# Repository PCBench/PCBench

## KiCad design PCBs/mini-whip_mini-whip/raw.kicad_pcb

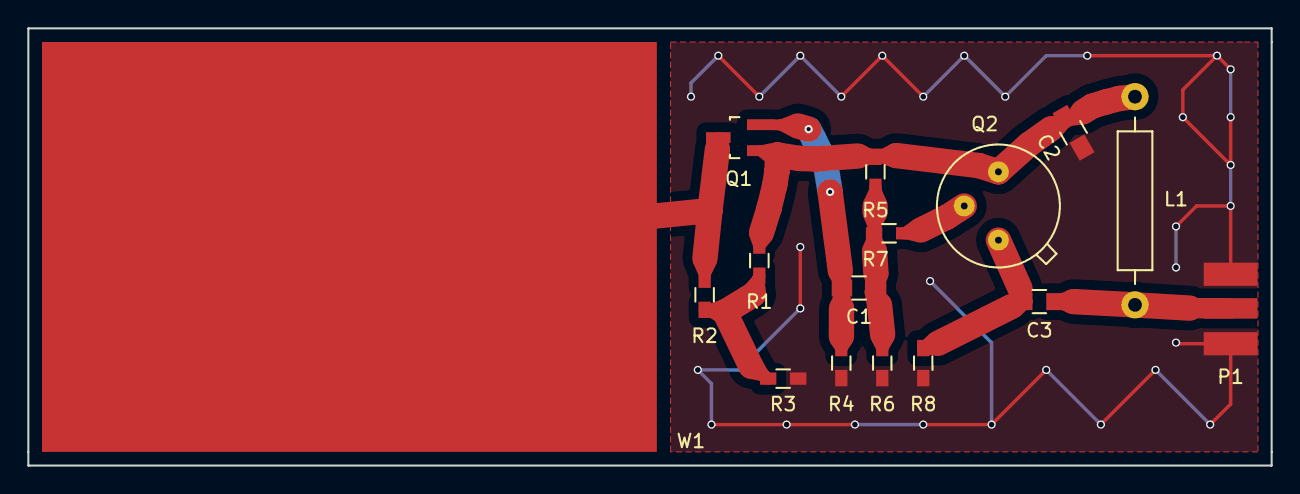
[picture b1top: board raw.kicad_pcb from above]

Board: 2 copper layers, 91.0 x 32.0 mm, 17 parts (1 on the bottom side), 9 nets.

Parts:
C1, C2, C3: 560n; C_0805_HandSoldering
L1: 470 uH; Choke_Horizontal_RM15mm
P1, P1#2: SMA-J
Q1: MMBFJ310; SOT-23_Handsoldering
Q2: 2N5109; M246
R1, R2, R3: 1M; R_0603_HandSoldering
R4: 680; R_0603_HandSoldering
R5: 2k2; R_0603_HandSoldering
R6: 10k; R_0603_HandSoldering
R7: 47; R_0603_HandSoldering
R8: 220; R_0603_HandSoldering
W1: MINIWHIP

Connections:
Earth: C2.1, P1.2, P1#2.2, R3.2, R4.2, R6.2, R8.2
unnamed: C1.1, R5.2, R6.1, R7.2
unnamed: C1.2, Q1.2, R4.1
unnamed: C2.2, L1.1, Q1.1, Q2.3, R1.1, R5.1
unnamed: C3.1, L1.2, P1.1, P1#2.1
unnamed: C3.2, Q2.1, R8.1
unnamed: Q1.3, R2.1, W1.1
unnamed: Q2.2, R7.1
unnamed: R1.2, R2.2, R3.1

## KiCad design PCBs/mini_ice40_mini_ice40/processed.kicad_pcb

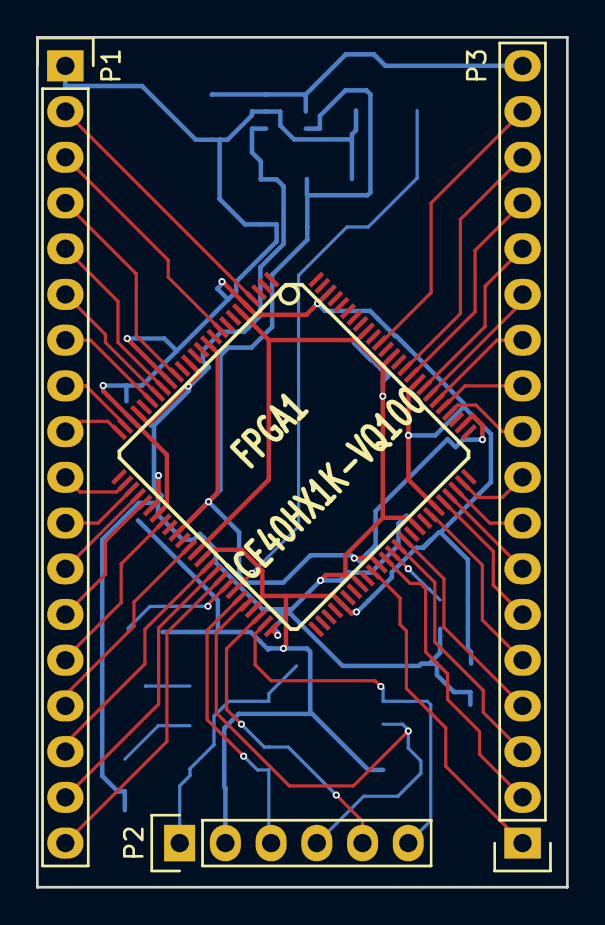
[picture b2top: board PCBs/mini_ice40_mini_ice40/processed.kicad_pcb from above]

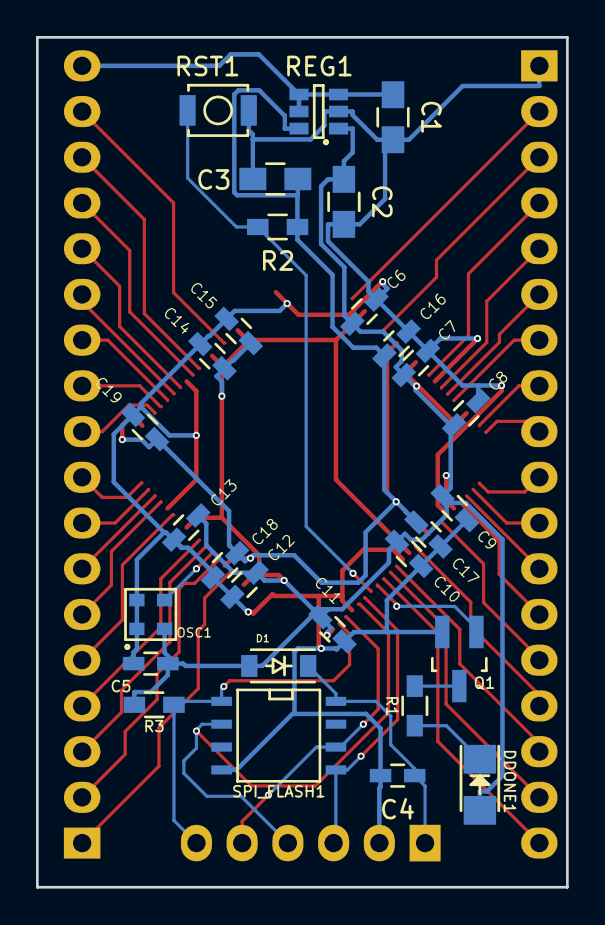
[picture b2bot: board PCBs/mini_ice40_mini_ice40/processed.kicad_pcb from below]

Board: 4 copper layers, 29.4 x 47.2 mm, 33 parts (29 on the bottom side), 48 nets.

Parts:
C1, C2, C3: 1u; C_0805_HandSoldering
C4, C5, C6, C7, C8, C9, C10, C11, C12, C13, C14, C15, C16, C17, C18, C19: 0u1; C_0603_HandSoldering
D1: 1N4448WQ-7-F; SOD-123
DDONE1: SML-LX1206GC-TR1; LED_1206
FPGA1: ICE40HX1K-VQ100; VQFP100
OSC1: ASDMB-26MHZ-LC; 2MMx2MM5
P1, P3: CONN_01X18; Pin_Header_Straight_1x18
P2: CONN_01X04; Pin_Header_Straight_1x06
Q1: 2N7002LT1G; SOT-23_Handsoldering
R1: 330; R_0603_HandSoldering
R2, R3: 10K; R_0603_HandSoldering
REG1: AP7312-1233W6-7; SOT-23-6
RST1: SW_PUSH; SW_SPST_B3U-1000P
SPI_FLASH1: AT25SF041-SSHD-B; SOIC-8-N

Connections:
+1V2: C3.1, C16.1, C17.1, C18.1, C19.1, FPGA1.11, FPGA1.35, FPGA1.61, FPGA1.77, R2.1, REG1.6
+3V3: C2.1, C5.1, C6.1, C7.1, C8.1, C9.1, C10.1, C11.1, C12.1, C13.1, C14.1, C15.1, D1.2, DDONE1.2, FPGA1.6, FPGA1.14, FPGA1.22, FPGA1.31, FPGA1.38, FPGA1.50, FPGA1.58, FPGA1.67, FPGA1.88, FPGA1.92, OSC1.4, R3.1, REG1.1
GND: C1.2, C2.2, C3.2, C4.2, C5.2, C6.2, C7.2, C8.2, C9.2, C10.2, C11.2, C12.2, C13.2, C14.2, C15.2, C16.2, C17.2, C18.2, C19.2, FPGA1.5, FPGA1.17, FPGA1.23, FPGA1.32, FPGA1.39, FPGA1.47, FPGA1.55, FPGA1.70, FPGA1.84, FPGA1.98, OSC1.1, OSC1.2, P1.1, P2.2, Q1.2, REG1.2, RST1.1, SPI_FLASH1.4
unnamed: C4.1, D1.1, P2.1, SPI_FLASH1.8
unnamed: DDONE1.1, R1.1
unnamed: FPGA1.4, P1.2
unnamed: FPGA1.9, P1.3
unnamed: FPGA1.16, P1.4
unnamed: FPGA1.18, P1.5
unnamed: FPGA1.19, P1.6
unnamed: FPGA1.20, P1.7
unnamed: FPGA1.24, P1.8
unnamed: FPGA1.25, P1.9
unnamed: FPGA1.27, P1.10
unnamed: FPGA1.28, P1.11
unnamed: FPGA1.29, P1.12
unnamed: FPGA1.30, P1.13
unnamed: FPGA1.33, P1.14
unnamed: FPGA1.37, P1.15
unnamed: FPGA1.40, P1.16
unnamed: FPGA1.41, P1.17
unnamed: FPGA1.42, P1.18
unnamed: FPGA1.43, Q1.1
unnamed: FPGA1.44, R2.2, RST1.2
unnamed: FPGA1.45, P2.3, SPI_FLASH1.5
unnamed: FPGA1.46, P2.4, SPI_FLASH1.2
unnamed: FPGA1.48, P2.5, SPI_FLASH1.6
unnamed: FPGA1.49, P2.6, R3.2, SPI_FLASH1.1
unnamed: FPGA1.60, P3.1
unnamed: FPGA1.62, P3.2
unnamed: FPGA1.63, OSC1.3
unnamed: FPGA1.64, P3.3
unnamed: FPGA1.65, P3.4
unnamed: FPGA1.69, P3.5
unnamed: FPGA1.71, P3.6
unnamed: FPGA1.72, P3.7
unnamed: FPGA1.73, P3.8
unnamed: FPGA1.74, P3.9
unnamed: FPGA1.79, P3.10
unnamed: FPGA1.80, P3.11
unnamed: FPGA1.81, P3.12
unnamed: FPGA1.82, P3.13
unnamed: FPGA1.83, P3.14
unnamed: FPGA1.85, P3.15
unnamed: FPGA1.86, P3.16
unnamed: FPGA1.90, P3.17
unnamed: Q1.3, R1.2
VCC: C1.1, P3.18, REG1.3, REG1.4, REG1.5

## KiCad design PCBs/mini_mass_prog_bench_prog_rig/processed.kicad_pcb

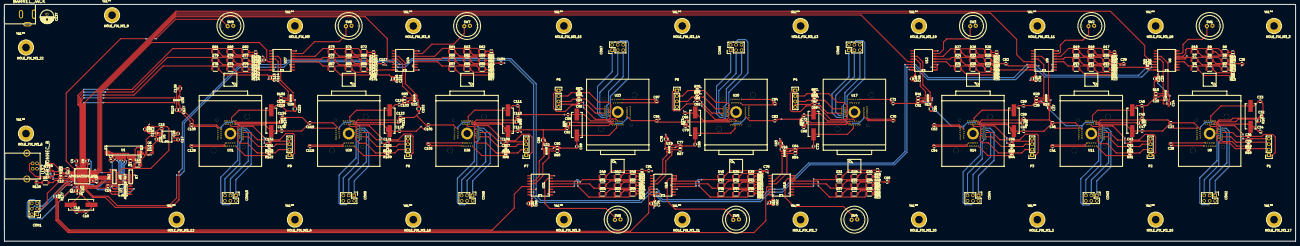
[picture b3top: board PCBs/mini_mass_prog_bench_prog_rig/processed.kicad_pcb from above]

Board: 4 copper layers, 600.0 x 110.0 mm, 441 parts (0 on the bottom side), 312 nets.

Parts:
C1, C2, C3, C4, C7, C8, C9, C10, C14, C15, C19, C22, C26, C27, C28, C29, C31, C32, C35, C39, C40, C41, C42, C44, C45, C48, C52, C53, C54, C55, C57, C58, C61, C65, C66, C67, C68, C70, C71, C74, C78, C79, C80, C81, C83, C84, C87, C91, C92, C93, C94, C96, C97, C100, C104, C105, C106, C107, C109, C110, C113, C117, C118, C119, C120, C122, C123, C128, C129, C130, C131, C133, C134, C135, C136: 100nF; C_0603
C5, C6: 22uF; C_1206
C11: 4.7uF; C_1206
C12, C25, C30, C38, C43, C51, C56, C64, C69, C77, C82, C90, C95, C103, C108, C116, C121, C127, C132: 1uF; C_0603
C13, C21: 4.7uF; C_0603
C16, C18, C33, C34, C46, C47, C59, C60, C72, C73, C85, C86, C98, C99, C111, C112, C124, C125: 18pF; C_0603
C17, C20: 220nF; C_0603
C23, C24, C36, C37, C49, C50, C62, C63, C75, C76, C88, C89, C101, C102, C114, C115, C126: 10uF; C_0805
C137: CP; C_Radial_D6.3_L11.2_P2.5
CON1, CON2, CON3, CON4, CON5, CON6, CON7, CON8, CON9, CON10: AVR-ISP-6; Pin_Header_Straight_2x03
CON11: BARREL_JACK; BARREL-PJ-002AH
D1, D2, D3, D4, D5, D6, D7, D8, D9, D10, D11, D12, D13, D14, D15, D16, D17, D18, D19, D20, D21, D22, D23, D24, D25, D26, D27, D28, D29, D30, D31, D32, D33, D34, D35, D36, D37, D38, D39, D40, D41, D42, D43, D44, D45, D46, D47, D48, D49, D50, D51, D52, D53, D54, D55, D56, D57, D58, D59, D60, D61, D62, D63, D64, D65, D66, D67, D68, D69, D70, D71, D72, D73, D74, D75, D76, D77, D78, D79, D80, D81, D82: LED; R_1206
HOLE_FIX_M3, HOLE_FIX_M3_2, HOLE_FIX_M3_3, HOLE_FIX_M3_4, HOLE_FIX_M3_5, HOLE_FIX_M3_6, HOLE_FIX_M3_7, HOLE_FIX_M3_8, HOLE_FIX_M3_9, HOLE_FIX_M3_10, HOLE_FIX_M3_11, HOLE_FIX_M3_12, HOLE_FIX_M3_13, HOLE_FIX_M3_14, HOLE_FIX_M3_15, HOLE_FIX_M3_16, HOLE_FIX_M3_17, HOLE_FIX_M3_18, HOLE_FIX_M3_19, HOLE_FIX_M3_20, HOLE_FIX_M3_21, HOLE_FIX_M3_22: VAL**; HOLE_FIX_M3
P1, P2, P3, P4, P5, P6, P7, P8, P9: CONN_01X04; Pin_Header_Straight_1x04
Q1: MOS_P; SOT23-3
R1: 910k; R_0603
R2, R3, R20, R33, R46, R59, R72, R85, R98, R111, R124, R127: 10k; R_0603
R4, R5, R18, R19, R31, R32, R44, R45, R57, R58, R70, R71, R83, R84, R96, R97, R109, R110, R122, R123: 22; R_0603
R6: 2k2; RNETWORK8_0603
R7: 4k7; RNETWORK8_0603
R8, R9, R10, R11, R12, R13, R14, R16, R17, R21, R22, R23, R24, R25, R26, R27, R29, R30, R34, R35, R36, R37, R38, R39, R40, R42, R43, R47, R48, R49, R50, R51, R52, R53, R55, R56, R60, R61, R62, R63, R64, R65, R66, R68, R69, R73, R74, R75, R76, R77, R78, R79, R81, R82, R86, R87, R88, R89, R90, R91, R92, R94, R95, R99, R100, R101, R102, R103, R104, R105, R107, R108, R112, R113, R114, R115, R116, R117, R118, R120, R121: R; R_0603
R15, R28, R41, R54, R67, R80, R93, R106, R119: 210k; R_0603
R125, R126: 2k2; R_0603
R128: 100; R_0603
SW1, SW2, SW3, SW4, SW5, SW6, SW7, SW8, SW9: SW_PUSH; SWITCH_K12P
U1: CON_UGM128032A6B01; CON_SFV24R-2STE1HLF
U2: ATMEGA32U4_QFN; QFN44
U3: AT45DB011D; SO8EN
U4: IP4234CZ6,125; TSOT-6-MK06A
U5: ST662ACD; SOIC-8-N
U6, U9, U12, U15, U18, U21, U24, U27: PCA9554; SO-16-L
U7, U10, U13, U16, U19, U22, U25, U28, U30: AP2552A; SOT-23-6
U8, U11, U14, U17, U20, U23, U26, U29, U31: ATMEGA32U4_QFN; QFN44_PROG_SOCKET
U32: USB_CONNEC_B; USB-AU-Y1007-R
Y1, Y2, Y3, Y4, Y5, Y6, Y7, Y8, Y9, Y10: 16MHz; Crystal_HC49-SD_SMD

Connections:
+3V3: C7.2, C12.1, C14.1, U1.5, U2.6, U3.3, U3.5, U3.6
+5V: C1.1, C2.1, C3.1, C4.1, C8.1, C13.1, C22.1, C23.1, C24.1, C26.1, C35.1, C36.1, C37.1, C39.1, C48.1, C49.1, C50.1, C52.1, C61.1, C62.1, C63.1, C65.1, C74.1, C75.1, C76.1, C78.1, C87.1, C88.1, C89.1, C91.1, C100.1, C101.1, C102.1, C104.1, C113.1, C114.1, C115.1, C117.1, C126.1, C128.1, C137.1, CON1.2, CON11.1, Q1.2, R2.1, R6.8, R8.1, R9.1, R10.1, R11.1, R12.1, R13.1, R14.1, R16.1, R17.1, R21.1, R22.1, R23.1, R24.1, R25.1, R26.1, R27.1, R29.1, R30.1, R34.1, R35.1, R36.1, R37.1, R38.1, R39.1, R40.1, R42.1, R43.1, R47.1, R48.1, R49.1, R50.1, R51.1, R52.1, R53.1, R55.1, R56.1, R60.1, R61.1, R62.1, R63.1, R64.1, R65.1, R66.1, R68.1, R69.1, R73.1, R74.1, R75.1, R76.1, R77.1, R78.1, R79.1, R81.1, R82.1, R86.1, R87.1, R88.1, R89.1, R90.1, R91.1, R92.1, R94.1, R95.1, R99.1, R100.1, R101.1, R102.1, R103.1, R104.1, R105.1, R107.1, R108.1, R112.1, R113.1, R114.1, R115.1, R116.1, R117.1, R118.1, R120.1, R121.1, R125.1, R126.1, U2.2, U2.14, U2.24, U2.34, U2.44, U6.16, U7.1, U9.1, U9.16, U10.1, U12.2, U12.16, U13.1, U15.1, U15.2, U15.16, U16.1, U18.3, U18.16, U19.1, U21.1, U21.3, U21.16, U22.1, U24.2, U24.3, U24.16, U25.1, U27.1, U27.2, U27.3, U27.16, U28.1, U30.1
+12V: C5.1, C6.1, C9.1, C19.1, C21.1, U1.23, U5.6
/BL_POWER: Q1.1, R6.7
/FLASH_HV_nS: R6.11, U2.28
/FLASH_nS: R6.6, R7.11, U3.4
/LCD_DnC: R6.3, R7.14, U1.10
/LCD_HV_DnC: R6.14, U2.25
/LCD_HV_SS: R6.12, U2.27
/LCD_HV_nRES: R6.13, U2.26
/LCD_SS: R6.5, R7.12, U1.8
/LCD_nRES: R6.4, R7.13, U1.9
/MISO: CON1.1, R127.1, U2.11
/MOSI: CON1.4, R3.1, U2.10
/Programming Socket #0/5V_SOCKET: C25.1, C27.1, C28.1, C29.1, C31.1, C32.1, CON2.2, R20.1, U7.6, U8.2, U8.14, U8.24, U8.34, U8.44
/Programming Socket #0/I2C_SCL: R125.2, U2.18, U6.14, U9.14, U12.14, U15.14, U18.14, U21.14, U24.14, U27.14
/Programming Socket #0/I2C_SDA: R126.2, U2.19, U6.15, U9.15, U12.15, U15.15, U18.15, U21.15, U24.15, U27.15
/Programming Socket #0/INT: U2.36, U6.13
/Programming Socket #0/LED1: D2.1, D3.1, D4.1, U6.4
/Programming Socket #0/LED2: D5.1, D6.1, D7.1, U6.5
/Programming Socket #0/LED3: D8.1, D9.1, D10.1, U6.6
/Programming Socket #0/PROG_MISO: CON2.1, U8.11
/Programming Socket #0/PROG_MOSI: CON2.4, U8.10
/Programming Socket #0/PROG_RESET: CON2.5, R20.2, U8.13
/Programming Socket #0/PROG_SCK: CON2.3, U8.9
/Programming Socket #0/PSU_EN: U6.11, U7.3
/Programming Socket #0/PSU_FAULT: U6.12, U7.4
/Programming Socket #0/SWITCH: SW1.1, U6.7
/Programming Socket #1/5V_SOCKET: C38.1, C40.1, C41.1, C42.1, C44.1, C45.1, CON3.2, R33.1, U10.6, U11.2, U11.14, U11.24, U11.34, U11.44
/Programming Socket #1/INT: U2.32, U9.13
/Programming Socket #1/LED1: D11.1, D12.1, D13.1, U9.4
/Programming Socket #1/LED2: D14.1, D15.1, D16.1, U9.5
/Programming Socket #1/LED3: D17.1, D18.1, D19.1, U9.6
/Programming Socket #1/PROG_MISO: CON3.1, U11.11
/Programming Socket #1/PROG_MOSI: CON3.4, U11.10
/Programming Socket #1/PROG_RESET: CON3.5, R33.2, U11.13
/Programming Socket #1/PROG_SCK: CON3.3, U11.9
/Programming Socket #1/PSU_EN: U9.11, U10.3
/Programming Socket #1/PSU_FAULT: U9.12, U10.4
/Programming Socket #1/SWITCH: SW2.1, U9.7
/Programming Socket #2/5V_SOCKET: C51.1, C53.1, C54.1, C55.1, C57.1, C58.1, CON4.2, R46.1, U13.6, U14.2, U14.14, U14.24, U14.34, U14.44
/Programming Socket #2/INT: U2.31, U12.13
/Programming Socket #2/LED1: D20.1, D21.1, D22.1, U12.4
/Programming Socket #2/LED2: D23.1, D24.1, D25.1, U12.5
/Programming Socket #2/LED3: D26.1, D27.1, D28.1, U12.6
/Programming Socket #2/PROG_MISO: CON4.1, U14.11
/Programming Socket #2/PROG_MOSI: CON4.4, U14.10
/Programming Socket #2/PROG_RESET: CON4.5, R46.2, U14.13
/Programming Socket #2/PROG_SCK: CON4.3, U14.9
/Programming Socket #2/PSU_EN: U12.11, U13.3
/Programming Socket #2/PSU_FAULT: U12.12, U13.4
/Programming Socket #2/SWITCH: SW3.1, U12.7
/Programming Socket #3/5V_SOCKET: C64.1, C66.1, C67.1, C68.1, C70.1, C71.1, CON5.2, R59.1, U16.6, U17.2, U17.14, U17.24, U17.34, U17.44
/Programming Socket #3/INT: R3.2, U15.13
/Programming Socket #3/LED1: D29.1, D30.1, D31.1, U15.4
/Programming Socket #3/LED2: D32.1, D33.1, D34.1, U15.5
/Programming Socket #3/LED3: D35.1, D36.1, D37.1, U15.6
/Programming Socket #3/PROG_MISO: CON5.1, U17.11
/Programming Socket #3/PROG_MOSI: CON5.4, U17.10
/Programming Socket #3/PROG_RESET: CON5.5, R59.2, U17.13
/Programming Socket #3/PROG_SCK: CON5.3, U17.9
/Programming Socket #3/PSU_EN: U15.11, U16.3
/Programming Socket #3/PSU_FAULT: U15.12, U16.4
/Programming Socket #3/SWITCH: SW4.1, U15.7
/Programming Socket #4/5V_SOCKET: C77.1, C79.1, C80.1, C81.1, C83.1, C84.1, CON6.2, R72.1, U19.6, U20.2, U20.14, U20.24, U20.34, U20.44
/Programming Socket #4/INT: R127.2, U18.13
/Programming Socket #4/LED1: D38.1, D39.1, D40.1, U18.4
/Programming Socket #4/LED2: D41.1, D42.1, D43.1, U18.5
/Programming Socket #4/LED3: D44.1, D45.1, D46.1, U18.6
/Programming Socket #4/PROG_MISO: CON6.1, U20.11
/Programming Socket #4/PROG_MOSI: CON6.4, U20.10
/Programming Socket #4/PROG_RESET: CON6.5, R72.2, U20.13
/Programming Socket #4/PROG_SCK: CON6.3, U20.9
/Programming Socket #4/PSU_EN: U18.11, U19.3
/Programming Socket #4/PSU_FAULT: U18.12, U19.4
/Programming Socket #4/SWITCH: SW5.1, U18.7
/Programming Socket #5/5V_SOCKET: C90.1, C92.1, C93.1, C94.1, C96.1, C97.1, CON7.2, R85.1, U22.6, U23.2, U23.14, U23.24, U23.34, U23.44
/Programming Socket #5/INT: U2.12, U21.13
/Programming Socket #5/LED1: D47.1, D48.1, D49.1, U21.4
/Programming Socket #5/LED2: D50.1, D51.1, D52.1, U21.5
/Programming Socket #5/LED3: D53.1, D54.1, D55.1, U21.6
/Programming Socket #5/PROG_MISO: CON7.1, U23.11
/Programming Socket #5/PROG_MOSI: CON7.4, U23.10
/Programming Socket #5/PROG_RESET: CON7.5, R85.2, U23.13
/Programming Socket #5/PROG_SCK: CON7.3, U23.9
/Programming Socket #5/PSU_EN: U21.11, U22.3
/Programming Socket #5/PSU_FAULT: U21.12, U22.4
/Programming Socket #5/SWITCH: SW6.1, U21.7
/Programming Socket #6/5V_SOCKET: C103.1, C105.1, C106.1, C107.1, C109.1, C110.1, CON8.2, R98.1, U25.6, U26.2, U26.14, U26.24, U26.34, U26.44
/Programming Socket #6/INT: U2.30, U24.13
/Programming Socket #6/LED1: D56.1, D57.1, D58.1, U24.4
/Programming Socket #6/LED2: D59.1, D60.1, D61.1, U24.5
/Programming Socket #6/LED3: D62.1, D63.1, D64.1, U24.6
/Programming Socket #6/PROG_MISO: CON8.1, U26.11
/Programming Socket #6/PROG_MOSI: CON8.4, U26.10
/Programming Socket #6/PROG_RESET: CON8.5, R98.2, U26.13
/Programming Socket #6/PROG_SCK: CON8.3, U26.9
/Programming Socket #6/PSU_EN: U24.11, U25.3
/Programming Socket #6/PSU_FAULT: U24.12, U25.4
/Programming Socket #6/SWITCH: SW7.1, U24.7
/Programming Socket #7/5V_SOCKET: C116.1, C118.1, C119.1, C120.1, C122.1, C123.1, CON9.2, R111.1, U28.6, U29.2, U29.14, U29.24, U29.34, U29.44
/Programming Socket #7/INT: U2.29, U27.13
/Programming Socket #7/LED1: D65.1, D66.1, D67.1, U27.4
/Programming Socket #7/LED2: D68.1, D69.1, D70.1, U27.5
/Programming Socket #7/LED3: D71.1, D72.1, D73.1, U27.6
/Programming Socket #7/PROG_MISO: CON9.1, U29.11
/Programming Socket #7/PROG_MOSI: CON9.4, U29.10
/Programming Socket #7/PROG_RESET: CON9.5, R111.2, U29.13
/Programming Socket #7/PROG_SCK: CON9.3, U29.9
/Programming Socket #7/PSU_EN: U27.11, U28.3
/Programming Socket #7/PSU_FAULT: U27.12, U28.4
/Programming Socket #7/SWITCH: SW8.1, U27.7
/Programming Socket #8/5V_SOCKET: C127.1, C129.1, C130.1, C131.1, C133.1, C134.1, CON10.2, R124.1, U30.6, U31.2, U31.14, U31.24, U31.34, U31.44
/Programming Socket #8/LED1: D74.1, D75.1, D76.1, U2.39
/Programming Socket #8/LED2: D77.1, D78.1, D79.1, U2.40
/Programming Socket #8/LED3: D80.1, D81.1, D82.1, U2.41
/Programming Socket #8/PROG_MISO: CON10.1, U31.11
/Programming Socket #8/PROG_MOSI: CON10.4, U31.10
/Programming Socket #8/PROG_RESET: CON10.5, R124.2, U31.13
/Programming Socket #8/PROG_SCK: CON10.3, U31.9
/Programming Socket #8/PSU_EN: U2.38, U30.3
/Programming Socket #8/PSU_FAULT: U2.37, U30.4
/Programming Socket #8/SWITCH: SW9.1, U2.1
/RESET: CON1.5, R2.2, U2.13
/SCK: CON1.3, U2.9
/SPI2_CLK: R6.2, R7.15, U1.13, U3.2
/SPI2_HV_MOSI: R6.16, U2.21
/SPI2_HV_SCK: R6.15, U2.22
/SPI2_MISO: U2.20, U3.8
/SPI2_MOSI: R6.1, R7.16, U1.14, U3.1
/USB_D+: R5.2, U2.4
/USB_D-: R4.2, U2.3
/USB_VBUS: C10.1, U2.7, U4.5, U32.1
GND: C1.2, C2.2, C3.2, C4.2, C5.2, C6.2, C7.1, C8.2, C9.2, C10.2, C11.2, C12.2, C13.2, C14.2, C15.2, C16.2, C18.2, C21.2, C22.2, C23.2, C24.2, C25.2, C26.2, C27.2, C28.2, C29.2, C30.2, C31.2, C32.2, C33.2, C34.2, C35.2, C36.2, C37.2, C38.2, C39.2, C40.2, C41.2, C42.2, C43.2, C44.2, C45.2, C46.2, C47.2, C48.2, C49.2, C50.2, C51.2, C52.2, C53.2, C54.2, C55.2, C56.2, C57.2, C58.2, C59.2, C60.2, C61.2, C62.2, C63.2, C64.2, C65.2, C66.2, C67.2, C68.2, C69.2, C70.2, C71.2, C72.2, C73.2, C74.2, C75.2, C76.2, C77.2, C78.2, C79.2, C80.2, C81.2, C82.2, C83.2, C84.2, C85.2, C86.2, C87.2, C88.2, C89.2, C90.2, C91.2, C92.2, C93.2, C94.2, C95.2, C96.2, C97.2, C98.2, C99.2, C100.2, C101.2, C102.2, C103.2, C104.2, C105.2, C106.2, C107.2, C108.2, C109.2, C110.2, C111.2, C112.2, C113.2, C114.2, C115.2, C116.2, C117.2, C118.2, C119.2, C120.2, C121.2, C122.2, C123.2, C124.2, C125.2, C126.2, C127.2, C128.2, C129.2, C130.2, C131.2, C132.2, C133.2, C134.2, C135.2, C136.2, C137.2, CON1.6, CON2.6, CON3.6, CON4.6, CON5.6, CON6.6, CON7.6, CON8.6, CON9.6, CON10.6, CON11.2, CON11.3, P1.4, P2.4, P3.4, P4.4, P5.4, P6.4, P7.4, P8.4, P9.4, R1.2, R7.1, R7.2, R7.3, R7.4, R7.5, R7.6, R15.1, R28.1, R41.1, R54.1, R67.1, R80.1, R93.1, R106.1, R119.1, R128.2, SW1.2, SW2.2, SW3.2, SW4.2, SW5.2, SW6.2, SW7.2, SW8.2, SW9.2, U1.2, U1.3, U1.6, U1.7, U1.11, U1.12, U1.16, U1.17, U1.18, U1.19, U1.20, U1.25, U1.26, U2.5, U2.15, U2.23, U2.35, U2.43, U2.45, U3.7, U4.2, U5.7, U5.8, U6.1, U6.2, U6.3, U6.8, U7.2, U8.5, U8.15, U8.23, U8.35, U8.43, U8.45, U9.2, U9.3, U9.8, U10.2, U11.5, U11.15, U11.23, U11.35, U11.43, U11.45, U12.1, U12.3, U12.8, U13.2, U14.5, U14.15, U14.23, U14.35, U14.43, U14.45, U15.3, U15.8, U16.2, U17.5, U17.15, U17.23, U17.35, U17.43, U17.45, U18.1, U18.2, U18.8, U19.2, U20.5, U20.15, U20.23, U20.35, U20.43, U20.45, U21.2, U21.8, U22.2, U23.5, U23.15, U23.23, U23.35, U23.43, U23.45, U24.1, U24.8, U25.2, U26.5, U26.15, U26.23, U26.35, U26.43, U26.45, U27.8, U28.2, U29.5, U29.15, U29.23, U29.35, U29.43, U29.45, U30.2, U31.5, U31.15, U31.23, U31.35, U31.43, U31.45, U32.4, U32.5, U32.6
unnamed: C11.1, U1.22
unnamed: C15.1, C19.2, Q1.3, U5.5
unnamed: C16.1, U2.16, Y1.1
unnamed: C17.1, U5.2
unnamed: C17.2, U5.1
unnamed: C18.1, U2.17, Y1.2
unnamed: C20.1, U5.3
unnamed: C20.2, U5.4
unnamed: C30.1, U8.6
unnamed: C33.1, U8.16, Y2.1
unnamed: C34.1, U8.17, Y2.2
unnamed: C43.1, U11.6
unnamed: C46.1, U11.16, Y3.1
unnamed: C47.1, U11.17, Y3.2
unnamed: C56.1, U14.6
unnamed: C59.1, U14.16, Y4.1
unnamed: C60.1, U14.17, Y4.2
unnamed: C69.1, U17.6
unnamed: C72.1, U17.16, Y5.1
unnamed: C73.1, U17.17, Y5.2
unnamed: C82.1, U20.6
unnamed: C85.1, U20.16, Y6.1
unnamed: C86.1, U20.17, Y6.2
unnamed: C95.1, U23.6
unnamed: C98.1, U23.16, Y7.1
unnamed: C99.1, U23.17, Y7.2
unnamed: C108.1, U26.6
unnamed: C111.1, U26.16, Y8.1
unnamed: C112.1, U26.17, Y8.2
unnamed: C121.1, U29.6
unnamed: C124.1, U29.16, Y9.1
unnamed: C125.1, U29.17, Y9.2
unnamed: C132.1, U31.6
unnamed: C135.1, U31.16, Y10.1
unnamed: C136.1, U31.17, Y10.2
unnamed: D1.1, R128.1
unnamed: D1.2, U2.8
unnamed: D2.2, R8.2
unnamed: D3.2, R9.2
unnamed: D4.2, R10.2
unnamed: D5.2, R11.2
unnamed: D6.2, R12.2
unnamed: D7.2, R13.2
unnamed: D8.2, R14.2
unnamed: D9.2, R16.2
unnamed: D10.2, R17.2
unnamed: D11.2, R21.2
unnamed: D12.2, R22.2
unnamed: D13.2, R23.2
unnamed: D14.2, R24.2
unnamed: D15.2, R25.2
unnamed: D16.2, R26.2
unnamed: D17.2, R27.2
unnamed: D18.2, R29.2
unnamed: D19.2, R30.2
unnamed: D20.2, R34.2
unnamed: D21.2, R35.2
unnamed: D22.2, R36.2
unnamed: D23.2, R37.2
unnamed: D24.2, R38.2
unnamed: D25.2, R39.2
unnamed: D26.2, R40.2
unnamed: D27.2, R42.2
unnamed: D28.2, R43.2
unnamed: D29.2, R47.2
unnamed: D30.2, R48.2
unnamed: D31.2, R49.2
unnamed: D32.2, R50.2
unnamed: D33.2, R51.2
unnamed: D34.2, R52.2
unnamed: D35.2, R53.2
unnamed: D36.2, R55.2
unnamed: D37.2, R56.2
unnamed: D38.2, R60.2
unnamed: D39.2, R61.2
unnamed: D40.2, R62.2
unnamed: D41.2, R63.2
unnamed: D42.2, R64.2
unnamed: D43.2, R65.2
unnamed: D44.2, R66.2
unnamed: D45.2, R68.2
unnamed: D46.2, R69.2
unnamed: D47.2, R73.2
unnamed: D48.2, R74.2
unnamed: D49.2, R75.2
unnamed: D50.2, R76.2
unnamed: D51.2, R77.2
unnamed: D52.2, R78.2
unnamed: D53.2, R79.2
unnamed: D54.2, R81.2
unnamed: D55.2, R82.2
unnamed: D56.2, R86.2
unnamed: D57.2, R87.2
unnamed: D58.2, R88.2
unnamed: D59.2, R89.2
unnamed: D60.2, R90.2
unnamed: D61.2, R91.2
unnamed: D62.2, R92.2
unnamed: D63.2, R94.2
unnamed: D64.2, R95.2
unnamed: D65.2, R99.2
unnamed: D66.2, R100.2
unnamed: D67.2, R101.2
unnamed: D68.2, R102.2
unnamed: D69.2, R103.2
unnamed: D70.2, R104.2
unnamed: D71.2, R105.2
unnamed: D72.2, R107.2
unnamed: D73.2, R108.2
unnamed: D74.2, R112.2
unnamed: D75.2, R113.2
unnamed: D76.2, R114.2
unnamed: D77.2, R115.2
unnamed: D78.2, R116.2
unnamed: D79.2, R117.2
unnamed: D80.2, R118.2
unnamed: D81.2, R120.2
unnamed: D82.2, R121.2
unnamed: P1.1, U8.7
unnamed: P1.2, R18.1
unnamed: P1.3, R19.1
unnamed: P2.1, U11.7
unnamed: P2.2, R31.1
unnamed: P2.3, R32.1
unnamed: P3.1, U14.7
unnamed: P3.2, R44.1
unnamed: P3.3, R45.1
unnamed: P4.1, U17.7
unnamed: P4.2, R57.1
unnamed: P4.3, R58.1
unnamed: P5.1, U20.7
unnamed: P5.2, R70.1
unnamed: P5.3, R71.1
unnamed: P6.1, U23.7
unnamed: P6.2, R83.1
unnamed: P6.3, R84.1
unnamed: P7.1, U26.7
unnamed: P7.2, R96.1
unnamed: P7.3, R97.1
unnamed: P8.1, U29.7
unnamed: P8.2, R109.1
unnamed: P8.3, R110.1
unnamed: P9.1, U31.7
unnamed: P9.2, R122.1
unnamed: P9.3, R123.1
unnamed: R1.1, U1.21
unnamed: R4.1, U4.4
unnamed: R5.1, U4.3
unnamed: R6.9, R6.10, U2.33
unnamed: R15.2, U7.5
unnamed: R18.2, U8.4
unnamed: R19.2, U8.3
unnamed: R28.2, U10.5
unnamed: R31.2, U11.4
unnamed: R32.2, U11.3
unnamed: R41.2, U13.5
unnamed: R44.2, U14.4
unnamed: R45.2, U14.3
unnamed: R54.2, U16.5
unnamed: R57.2, U17.4
unnamed: R58.2, U17.3
unnamed: R67.2, U19.5
unnamed: R70.2, U20.4
unnamed: R71.2, U20.3
unnamed: R80.2, U22.5
unnamed: R83.2, U23.4
unnamed: R84.2, U23.3
unnamed: R93.2, U25.5
unnamed: R96.2, U26.4
unnamed: R97.2, U26.3
unnamed: R106.2, U28.5
unnamed: R109.2, U29.4
unnamed: R110.2, U29.3
unnamed: R119.2, U30.5
unnamed: R122.2, U31.4
unnamed: R123.2, U31.3
unnamed: U4.6, U32.2
unnamed: U4.1, U32.3

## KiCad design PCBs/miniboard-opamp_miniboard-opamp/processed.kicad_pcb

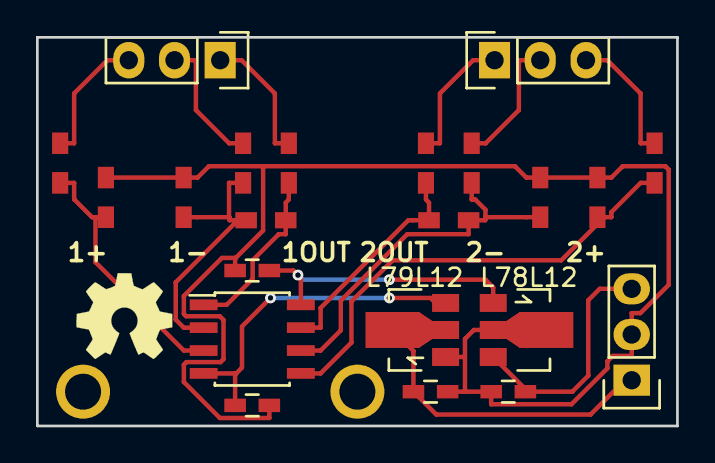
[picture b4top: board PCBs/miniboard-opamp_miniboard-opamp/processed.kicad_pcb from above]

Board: 2 copper layers, 35.6 x 21.6 mm, 25 parts (0 on the bottom side), 17 nets.

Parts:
C1, C2: 330n; C_0603_HandSoldering
C3, C4: 100n; C_0603_HandSoldering
P1, P3, P4: CONN_01X03; Socket_Strip_Straight_1x03
R1, R2, R3, R4, R5, R6, R7, R8, R9, R10, R11, R12: R; R_0603_nodraw
U1: L78L12; SOT89-3_Housing
U2: L79L12; SOT89-3_Housing
U3: TL072; SOIC-8_3.9x4.9mm_Pitch1.27mm
hole_2mm, hole_2mm_2, hole_2mm_3: VAL**; hole_2mm

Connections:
/12_filter: C3.1, U1.1, U3.8
/-12_filter: C4.2, U2.3, U3.4
GND: C1.2, C2.1, C3.2, C4.1, P1.2, R3.2, R4.1, R8.2, R9.1, U1.2, U2.1
unnamed: C1.1, P1.3, U1.3
unnamed: C2.2, P1.1, U2.2
unnamed: P3.1, R11.2
unnamed: P3.2, R2.2
unnamed: P3.3, R1.2
unnamed: P4.1, R12.2
unnamed: P4.2, R7.2
unnamed: P4.3, R6.2
unnamed: R1.1, R3.1, U3.3
unnamed: R2.1, R4.2, R5.2, U3.2
unnamed: R6.1, R8.1, U3.5
unnamed: R10.1, R12.1, U3.7
unnamed: R7.1, R9.2, R10.2, U3.6
unnamed: R5.1, R11.1, U3.1

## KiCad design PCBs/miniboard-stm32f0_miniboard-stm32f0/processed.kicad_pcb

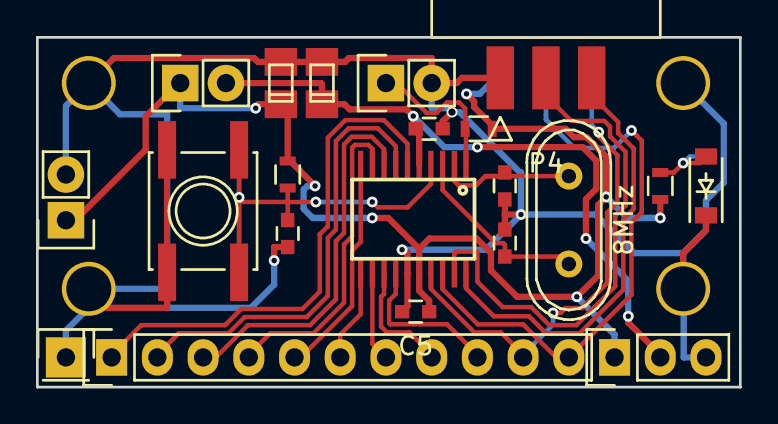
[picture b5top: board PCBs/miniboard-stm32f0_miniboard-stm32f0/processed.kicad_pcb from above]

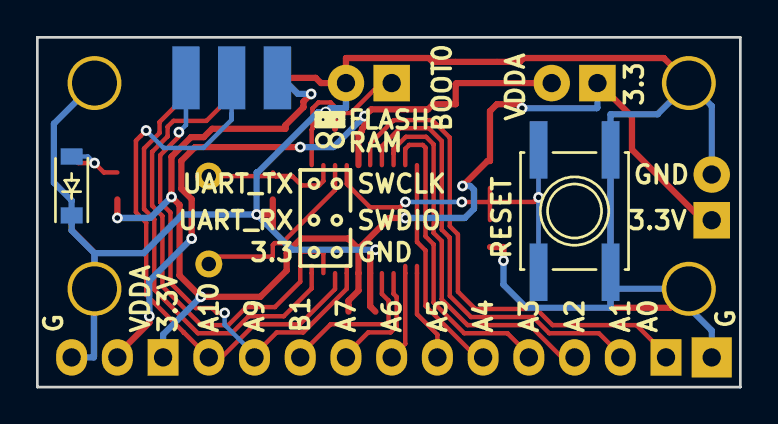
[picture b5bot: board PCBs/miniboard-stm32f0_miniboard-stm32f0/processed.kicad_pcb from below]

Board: 2 copper layers, 39.1 x 19.4 mm, 27 parts (2 on the bottom side), 21 nets.

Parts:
C1, C2, C3: 20pF; C_0603
C4: 4.7uF; TantalC_SizeR_EIA-2012
C5: 100pF; C_0603
C6: 1uF; TantalC_SizeR_EIA-2012
C7: 10pF; C_0603
D1, D2: LED; SOD-123
H1, H2, H3, H4: HOLE; hole_2.5mm
P1: CONN_01X02; Pin_Header_Straight_1x02
P2: CONN_01X11; Pin_Header_Straight_1x11
P3: CONN_01X01; Pin_Header_Straight_1x01
P4: CONN_02X03; pin_header_edge_6
P_BOOT0: CONN_01X02; Pin_Header_Straight_1x02
P_POWER1: CONN_01X02; Pin_Header_Straight_1x02
P_POWER_BOARD1: CONN_01X03; Pin_Header_Straight_1x03
R1, R2, R3: 4.7k; R_0603
SW1, SW2: SW_PUSH; SW_SPST_EVQQ2
U1: stm32f030f4p6; tssop20
Y1: 8MHz; Crystal_HC49-U_Vertical

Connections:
+3V3: C4.1, C5.1, P1.1, P4.2, P_POWER1.1, P_POWER_BOARD1.1, R1.1, R2.1, R3.1, U1.16
/BOOT0: P_BOOT0.1, R1.2, U1.1
/NRST: C3.1, R2.2, SW1.2, SW2.2, U1.4
/OSC_IN: C1.1, U1.2, Y1.1
/OSC_OUT: C2.1, U1.3, Y1.2
/PA0: P2.1, U1.6
/PA1: P2.2, U1.7
/PA2: P2.3, U1.8
/PA3: P2.4, U1.9
/PA4: P2.5, U1.10
/PA5: P2.6, U1.11
/PA6: P2.7, U1.12
/PA7: P2.8, U1.13
/PA9_TX: P2.10, P4.6, U1.17
/PA10_RX: P2.11, P4.4, U1.18
/PA13_SWDIO: P4.3, U1.19
/PA14_SWCLK: P4.5, U1.20
/PB1: P2.9, U1.14
GND: C1.2, C2.2, C3.2, C4.2, C5.2, C6.2, C7.2, D1.1, D2.1, H1.1, H2.1, H3.1, H4.1, P3.1, P4.1, P_BOOT0.2, P_POWER1.2, P_POWER_BOARD1.3, SW1.1, SW2.1, U1.15
unnamed: D1.2, D2.2, R3.2
VAA: C6.1, C7.1, P1.2, P_POWER_BOARD1.2, U1.5

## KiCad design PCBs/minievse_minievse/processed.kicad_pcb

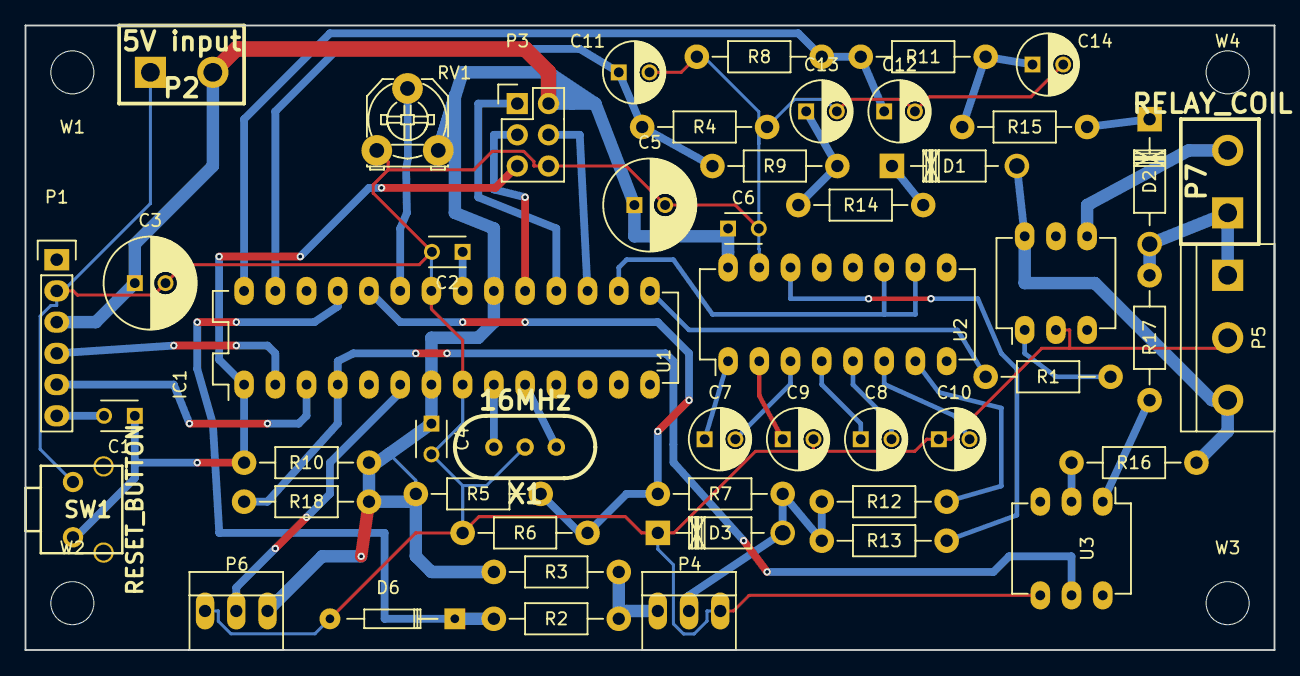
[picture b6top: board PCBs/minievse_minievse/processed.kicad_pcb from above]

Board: 2 copper layers, 101.6 x 50.8 mm, 54 parts (0 on the bottom side), 41 nets.

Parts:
C1, C2, C4, C6: 104; C_Disc_D3_P2.5
C3, C5: 100uF; C_Radial_D7.5_L11.2_P2.5
C7, C8, C9, C10: 1uF; C_Radial_D5_L6_P2.5
C11, C12, C13, C14: 10uF; C_Radial_D5_L6_P2.5
D1, D2: 1N4007; Diode_DO-41_SOD81_Horizontal_RM10_refdes_in_box
D3: P6KE16CA; Diode_DO-41_SOD81_Horizontal_RM10_refdes_in_box
D6: 1N4148; Diode_DO-35_SOD27_Horizontal_RM10
IC1: ATMEGA328P-P; DIP-28_W7.62mm_LongPads
P1: SERIAL; Pin_Header_Straight_1x06
P2: 5V input; CCFLHV
P3: ICSP; Pin_Header_Straight_2x03
P4: Pilot; PINHEAD1-3
P5: AC_GND_AC; bornier3
P6: LED_STRIP; PINHEAD1-3
P7: RELAY_COIL; CCFLHV
R1: 220; Resistor_Horizontal_RM10mm_refdes_in_box
R2, R10, R18: 10K; Resistor_Horizontal_RM10mm_refdes_in_box
R3: 1K; Resistor_Horizontal_RM10mm_refdes_in_box
R4, R8, R9, R11: 2550; Resistor_Horizontal_RM10mm_refdes_in_box
R5: 56K; Resistor_Horizontal_RM10mm_refdes_in_box
R6: 100K; Resistor_Horizontal_RM10mm_refdes_in_box
R7: 200K; Resistor_Horizontal_RM10mm_refdes_in_box
R12, R13: 1200; Resistor_Horizontal_RM10mm_refdes_in_box
R14, R15: 50K; Resistor_Horizontal_RM10mm_refdes_in_box
R16, R17: 15K; Resistor_Horizontal_RM10mm_refdes_in_box
RV1: POT; Potentiometer_Triwood_RM-065
SW1: RESET_BUTTON; SW-1825027-5
U1: MAX232; DIP-16_W7.62mm_LongPads
U2: MOC3021M; DIP-6_W7.62mm_LongPads
U3: H11AA; DIP-6_W7.62mm_LongPads
W1, W2, W3, W4: MountingHole_3.5mm
X1: 16MHz; HC-49V-OR-RESONATOR

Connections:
+5VD: C3.1, C4.1, C5.1, C6.1, IC1.7, IC1.20, P1.3, P2.2, P3.2, P6.3, R3.2, R5.1, R10.1, R18.1, RV1.3, U1.16
/AC_SENSE_1: C11.1, IC1.27, R4.1, R9.2
/AC_SENSE_2: C12.1, IC1.28, R8.1, R11.2
/AC_ZEROX: IC1.4, R18.2, U3.5
/AMP_KNOB: IC1.23, RV1.2
/LED_DATA: IC1.6, P6.2
/PILOT: D3.2, P4.2, R7.1, R12.1, R13.1
/PILOTREAD: IC1.24, R5.2, R6.1, R7.2
/PP: P4.1, R2.2, R3.1
/PP_READ: D6.1, IC1.25, R2.1
/PWM: IC1.16, U1.10, U1.11
/RELAY_TRIAC: IC1.15, R1.2
/RX: IC1.2, P1.4
/TX: IC1.3, P1.5
/miso: IC1.18, P3.1
/mosi: IC1.17, P3.4
/reset: C1.1, IC1.1, P3.5, R10.2, SW1.1
/sck: IC1.19, P3.3
GND: C2.2, C3.2, C4.2, C5.2, C6.2, C9.2, C10.1, C11.2, C12.2, C13.2, C14.2, D3.1, D6.2, IC1.8, IC1.22, P1.2, P2.1, P3.6, P4.3, P5.2, P6.1, R4.2, R6.2, R8.2, RV1.1, SW1.2, U1.15, U2.2, U3.4, X1.3
unnamed: C1.2, P1.6
unnamed: C2.1, IC1.21
unnamed: C7.1, U1.1
unnamed: C7.2, U1.3
unnamed: C8.1, U1.4
unnamed: C8.2, U1.5
unnamed: C9.1, U1.2
unnamed: C10.2, U1.6
unnamed: C13.1, R9.1, R14.1
unnamed: C14.1, R11.1, R15.1
unnamed: D2.2, P5.1, P7.1, R17.2
unnamed: D1.1, R14.2
unnamed: D1.2, P5.3, R16.2, U2.6
unnamed: D2.1, R15.2
unnamed: IC1.9, X1.2
unnamed: IC1.10, X1.1
unnamed: P7.2, U2.4
unnamed: R1.1, U2.1
unnamed: R12.2, U1.7
unnamed: R13.2, U1.14
unnamed: R16.1, U3.2
unnamed: R17.1, U3.1

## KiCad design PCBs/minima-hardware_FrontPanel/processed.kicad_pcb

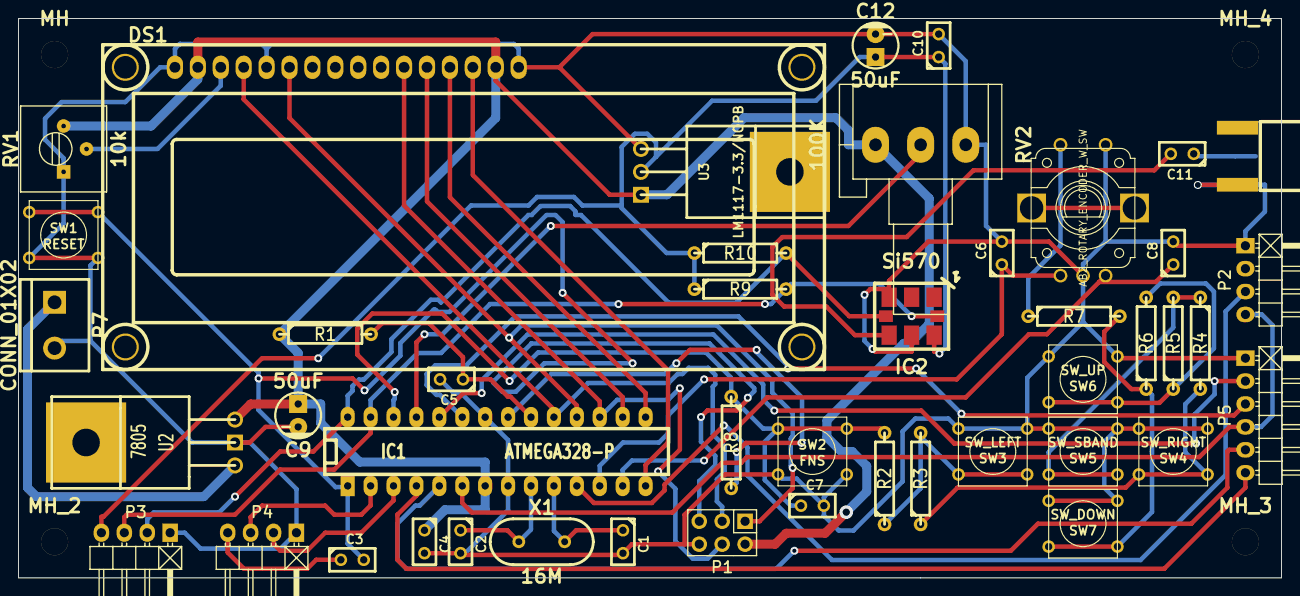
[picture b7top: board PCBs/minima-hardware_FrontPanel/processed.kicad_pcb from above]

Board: 2 copper layers, 140.0 x 62.0 mm, 49 parts (0 on the bottom side), 39 nets.

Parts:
C1, C2: 22pF; C1
C3: 0.1; C1
C4, C5: C; C1
C6, C7, C8: 1nF; C1
C9, C12: 50uF; Capacitor5x6RM2.5
C10, C11: .1uF; C1
DS1: LCD16X2; WC1602A
IC1: ATMEGA328-P; DIP-28__300_ELL
IC2: Si570; SI570_SI571_Standard
J1: sma; SMA_EDGE
MH: MountingHole_3mm_RevA_Date21Jun2010; MountingHole_3mm
MH_2, MH_3, MH_4: MountingHole_3mm_RevA_Date21Jun2010; MountingHole_3mm
P1: ICSP; Pin_Header_Straight_2x03
P2, P3, P4: CONN_01X04; Pin_Header_Angled_1x04
P5: CONN_01X06; Pin_Header_Angled_1x06
P7: CONN_01X02; bornier2
R1: 100K; R4
R2, R3, R4, R5, R6, R7: 4.7k; R4
R8: 47k; R4
R9, R10: 4.7K; R4
ROT_ENC1: AB2_ROTARY_ENCODER_W_SW; AB2_ROTARY_ENCODER_W_SWITCH
RV1: 10k; Potentiometer_Trimmer-Suntan-TSR-3386P
RV2: 100K; Potentiometer_Alps-RK16-single_largePads
SW1: RESET; SW_PUSH_SMALL
SW2: FNS; SW_PUSH_SMALL
SW3: SW_LEFT; SW_PUSH_SMALL
SW4: SW_RIGHT; SW_PUSH_SMALL
SW5: SW_SBAND; SW_PUSH_SMALL
SW6: SW_UP; SW_PUSH_SMALL
SW7: SW_DOWN; SW_PUSH_SMALL
U2: 7805; LM78XX
U3: LM1117-3.3/NOPB; TO220
X1: 16M; HC-49V

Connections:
+3.3V: C10.1, C12.1, IC2.6, P3.4, R9.1, R10.1, U3.3
+12V: P7.1, U2.VI
/D4: DS1.11, IC1.17, P1.4
/D5: DS1.12, IC1.16
/D6: DS1.13, IC1.15
/D7: DS1.14, IC1.14
/E: DS1.6, IC1.18, P1.1
/RS: DS1.4, IC1.19, P1.3
/TUNE: IC1.25, RV2.2
CWTONE: IC1.5, P5.5
GND: C1.2, C2.2, C4.2, C5.2, C6.2, C7.2, C8.2, C9.2, C10.2, C12.2, DS1.1, DS1.5, DS1.16, IC1.8, IC1.22, IC2.3, IC2.5, J1.2, P1.6, P2.1, P3.1, P4.1, P5.1, P7.2, ROT_ENC1.2, ROT_ENC1.4, RV1.1, RV2.1, SW1.2, SW2.2, SW3.2, SW4.2, SW5.2, SW6.2, SW7.2, U2.GND, U3.2
KEY: IC1.24, P5.2
unnamed: C1.1, IC1.10, X1.2
unnamed: C2.1, IC1.9, X1.1
unnamed: C3.2, IC1.1, P1.5, SW1.1
unnamed: C5.1, IC1.20, R1.2
unnamed: C6.1, IC1.12, ROT_ENC1.1
unnamed: C7.1, IC1.26, R2.2, R8.1, SW2.1
unnamed: C8.1, IC1.13, ROT_ENC1.3
unnamed: C11.1, J1.1
unnamed: C11.2, IC2.4
unnamed: DS1.3, RV1.2
unnamed: IC1.21, R8.2
unnamed: R2.1, R3.2, SW3.1
unnamed: R3.1, R4.2, SW4.1
unnamed: R4.1, R5.2, SW5.1
unnamed: R5.1, R6.2, SW6.1
unnamed: R6.1, R7.2, SW7.1
unnamed: R7.1, ROT_ENC1.6
PTT: IC1.23, P5.3
RF386: IC1.11, P2.3
RTS: C3.1, P4.4
RX: IC1.3, P4.2
SCL: IC1.28, IC2.8, P3.2, R10.2
SDA: IC1.27, IC2.7, P3.3, R9.2
TX: IC1.2, P4.3
TX/RX: IC1.6, P2.4, P5.4
USB/LSB: IC1.4, P5.6
VCC: C4.1, C9.1, DS1.2, DS1.15, IC1.7, P1.2, R1.1, RV1.3, RV2.3, U2.VO, U3.1
